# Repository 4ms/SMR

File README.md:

# SMR
## Spectral Multiband Resonator

Firmware for the Spectral Multiband Resonator, a Eurorack-format module from 4ms Company.

The SMR is a 6-channel highly resonant filter ("resonator") with a ring of RGB LEDs, six sliders, and stereo audio inputs and outputs. The main processor is the STM32F427 chip. For more details see http://www.4mspedals.com/smr.php

The SMR would make a nice platform for other audio projects, the hardware contains:

*	180MHz 32-bit ARM chip with FPU (STM32F427)
*	Stereo codec chip (running at 96kHz/24bit in this firmware)
	*	Two audio inputs, two audio outputs
*	Five 16-channel PCA9685 LED drivers (10-bits per channel)  
*	26 RGB LEDs, 20 are arranged in a circle/ellipse, 6 are arranged in a line  
*	Six slider potentiometers with an LED on the shaft  
*	Five potentiometers  
*	Six momentary LED buttons  
*	A rotary encoder and button  
*	Six toggle switches (one is SP3T, others are SPST)  
*	Twelve CV inputs
*	Six gate/digital inputs (can be used as unscaled CV inputs)
*	Six CV outputs (0V-8V), driven by PWM  
  
As of writing this (March 2016), there are three PCB versions: 1.0, 1.0.1, and 1.0.2. These are functionally identical and this firmware will run exactly the same on all versions.

## Setting up your environment
You need to install the GCC ARM toolchain.
This project is known to compile with arm-none-eabi-gcc version 4.8.3, and version 4.9.3. It is likely that it will compile with future versions as well.

It's recommended (but not necessary) to install ST-UTIL/stlink. Without it, you will have to update using the audio bootloader, which is very slow (5 minutes per update).
With ST-UTIL or stlink and a programmer, you can update in 5-20 seconds.
The Texane stlink package contains a gdb debugger, which works with ST-LINK programmers such as the [STM32 Discovery boards](http://www.mouser.com/ProductDetail/STMicroelectronics/STM32F4DISCOVERY/?qs=J2qbEwLrpCGdWLY96ibNeQ%3D%3D&gclid=CKb6u6Cz48cCFZGBfgodfHwH-g&kpid=608656256) to connect to the Spectral's 4-pin SWD header. The STM32F4 Discovery Board is low-cost (under US$15) and works great as a programmer and debugger.

You also may wish to install and IDE such as Eclipse. There are many resources online for setting up GCC ARM with Eclipse (as well as commerical software). This is totally optional. Instead of an IDE you can use your favorite text editor and a few commands on the command line (Terminal) which are given below.

Continue below for Max OSX, Linux, or Windows instructions.

### Mac OSX

For Mac OSX, follow these instructions to install brew and then the arm toolchain and st-link (taken from https://github.com/nitsky/homebrew-stm32):

	ruby -e "$(curl -fsSL https://raw.githubusercontent.com/Homebrew/install/master/install)"
	brew tap nitsky/stm32
	brew install arm-none-eabi-gcc
	brew install stlink

That's it! Continue below to **Clone the Projects**

### Linux

For linux, check your package manager to see if there is a package for arm-none-eabi-gcc or gcc-arm-embedded or gcc-arm-none-eabi. Or just download it here:

[Download GCC ARM toolchain from Launchpad](https://launchpad.net/gcc-arm-embedded/+download)

Next, install st-link from texane:

	sudo apt-get install git libusb-1.0.0-dev pkg-config autotools-dev
	cd (your work directory)
	git clone https://github.com/texane/stlink.git
	cd stlink
	./autogen.sh
	./configure
	make
	export PATH=$PATH:(your work directory)/stlink

The last command makes sure that the binary st-flash is in your PATH so that the Makefile can run it to program your module. 
 
That's it! Continue below to **Clone the Projects**

### Windows
[Download GCC ARM toolchain from Launchpad](https://launchpad.net/gcc-arm-embedded/+download)

[Download ST-UTIL](http://www.st.com/web/en/catalog/tools/PF258168)

Install both. Please contact me if you run into problems that you can't google your way out of! 

## Clone the Projects

Make sure git is installed on your system. (OSX: type "brew install git" into the Terminal)

Create a work directory, and enter it.

Clone this project (SMR), stmlib, and the stm-audio-bootloader projects:

	git clone https://github.com/4ms/SMR.git  
	git clone https://github.com/4ms/stmlib.git
	git clone https://github.com/4ms/stm-audio-bootloader.git
	
Create a symlink for stm-audio-bootloader so that it works with python (required to generate the .wav file for audio bootloading)

     ln -s stm-audio-bootloader stm_audio_bootloader

Verify that your directories are as follows:

	(work directory)
	|  
	|--SMR/  
	|--stm-audio-bootloader/  
	|--stm_audio_bootloader/   <----symlink to stm-audio-bootloader
	|--stmlib/

## Compiling
Make your changes to the code in the SMR directory. When ready to compile, make the project like this:

	cd SMR
	make

If you want to flash the file onto the SMR, attach an [ST-LINK programmer](http://www.st.com/web/catalog/tools/FM116/SC959/SS1532/PF252419) in SWD mode using a 4-conductor cable and run:

	make flash

Read the Discovery Board's manual for how to set it to program external devices. On the STM32F4 Discovery board, you have to remove two DISCOVERY jumpers to put it in ST-LINK mode. Connect the 4-pin cable to the SWD header starting at the dot (pin 1) on the Disco board. On the SMR, pin 1 is labeled with a "1". Any 4-pin cable or even 4 breadboard jumper wires will work. A 10-to-16 pin eurorack power cable is fine too, if it's short enough.

When ready to build an audio file for the bootloader, make it like this:

	make wav

This requires python to run. It creates the file main.wav in the build/ directory. Play the file from a computer or device into the SMR by following the instructions in the User Manual on the [4ms SMR page](http://4mscompany.com/smr.php). 

Troubleshooting: If you have trouble getting python to create a wav file, such as this error:

	ImportError: No module named stm_audio_bootloader

Then try this command:
	
	export PYTHONPATH=$PYTHONPATH:'.'

## Bootloader
The bootloader is a [separate project](https://github.com/4ms/stm-audio-bootloader), slightly modifed from the stm-audio-bootloader from [pichenettes](https://github.com/pichenettes/eurorack). 

The bootloader is already installed on all factory-built SMRs.

## License
The code (software) is licensed by the MIT license.

The hardware is licensed by the [CC BY-NC-SA license](https://creativecommons.org/licenses/by-nc-sa/4.0/) (Creative Commons, Attribution, NonCommercial, ShareAlike).

See LICENSE file.

I would like to see others build and modify the SMR and SMR-influenced works, in a non-commercial manner. My intent is not to limit the educational use nor to prevent people buying hardware components/PCBs collectively in a group. If you have any questions regarding the license or appropriate use, please do not hesitate to contact me! 

## Guidelines for derivative works

Do not include the text "4ms" or "4ms Company" or the graphic 4ms logo on any derivative works. This includes faceplates, enclosures, or front-panels. It's OK (but not required) to include the text "Spectral Multiband Resonator" or "SMR" if you wish.

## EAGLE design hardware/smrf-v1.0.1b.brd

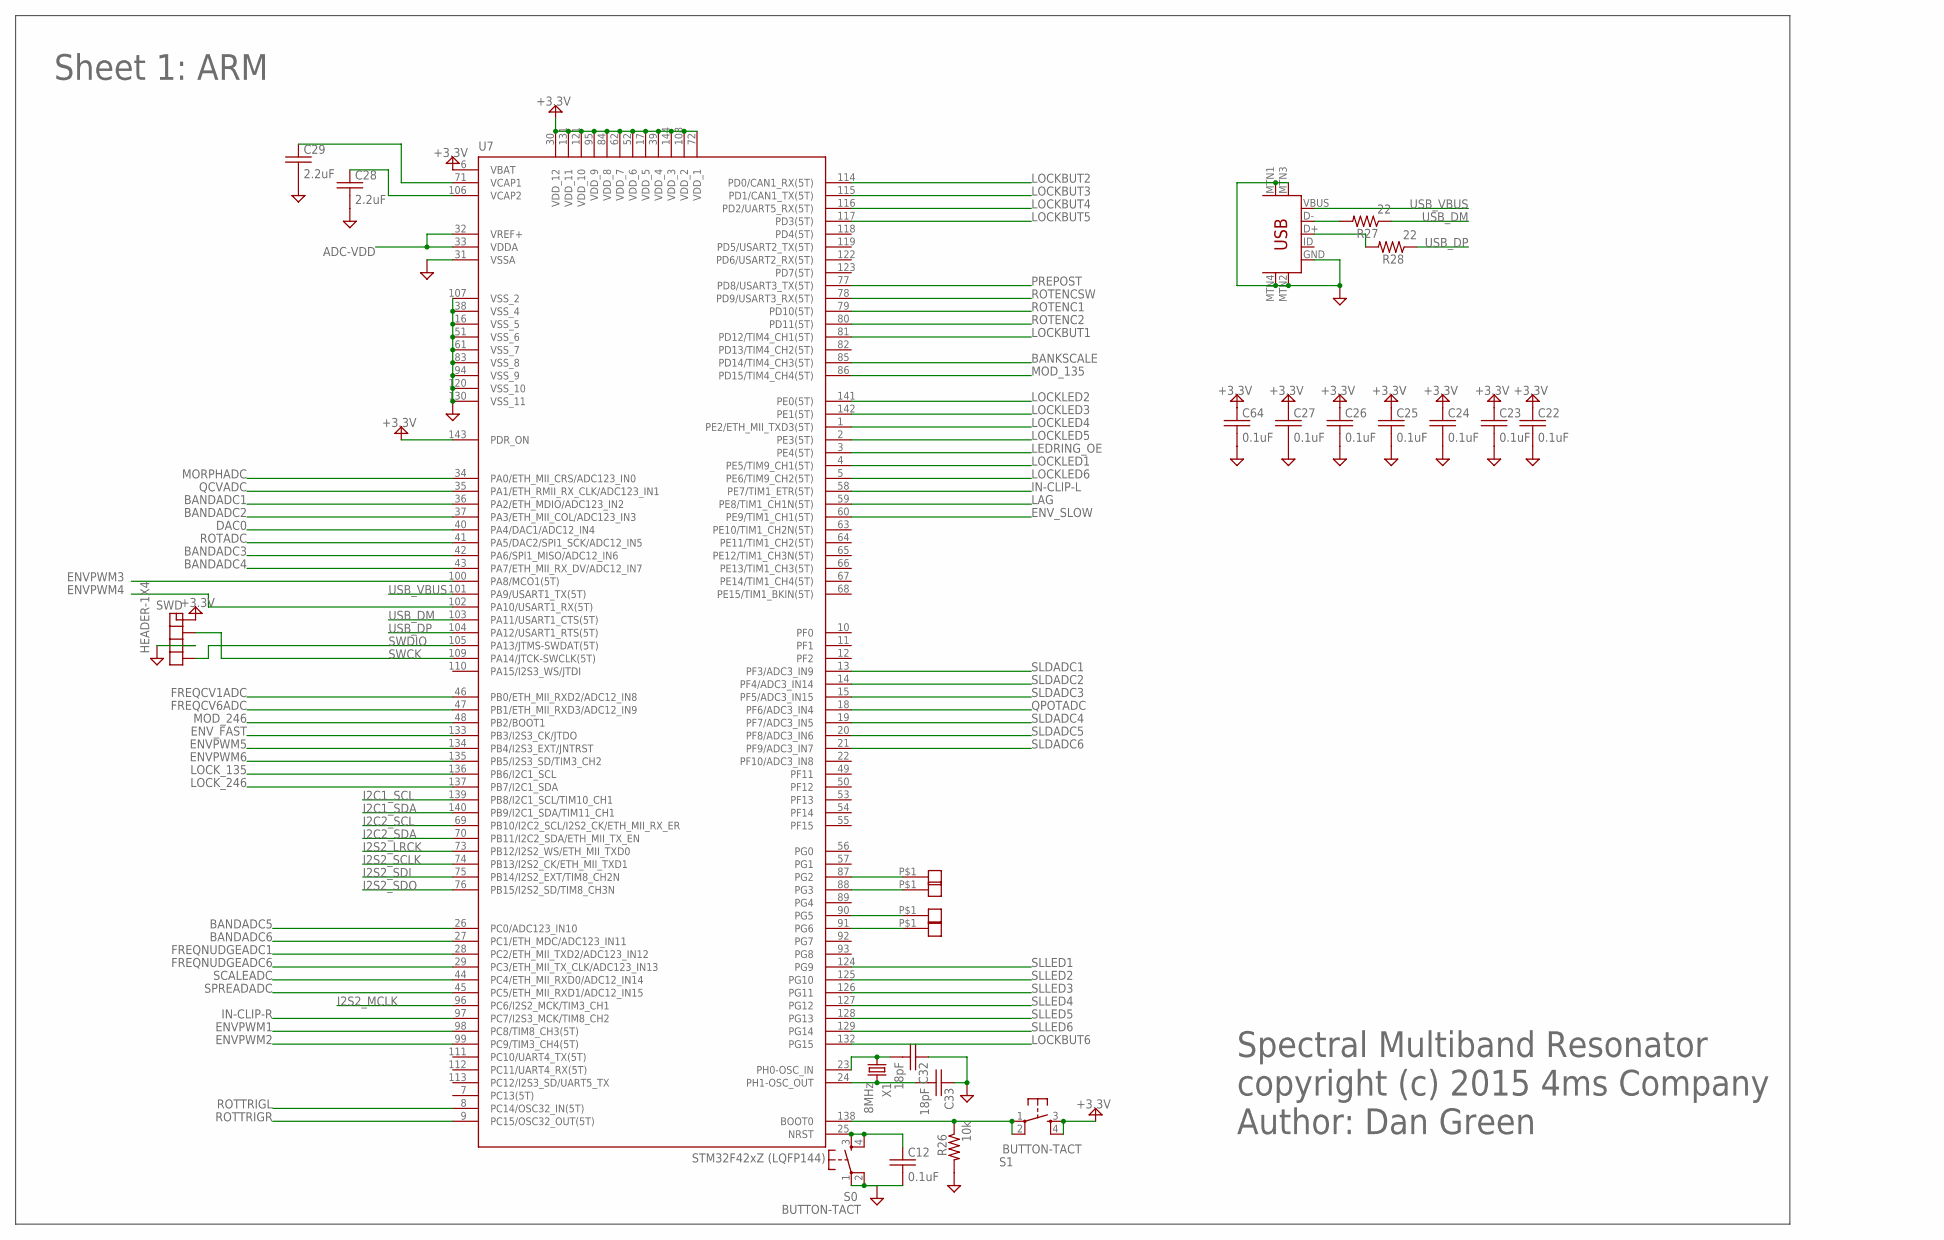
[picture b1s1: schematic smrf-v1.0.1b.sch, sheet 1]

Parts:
C12, C22, C23, C24, C25, C26, C27, C64: 0.1uF; C0603
C28, C29: 2.2uF; C0603
C32, C33: 18pF; C0603
PG2, PG3, PG5, PG6: PAD-06
R26: 10k; R0603
R27, R28: 22; R0603
S0, S1: BUTTON-TACT; BUTTON-TACT-SKQG
SWD: HEADER-1X4; HEADER-1X4-TH
U7: STM32F427ZG; LQFP144
U$1: USB-MINIB-5PIN; USB-MINIB
X1: 8MHz; HC-49/US

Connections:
+3.3V: C22.1, C23.1, C24.1, C25.1, C26.1, C27.1, C64.1, S1.3, S1.4, SWD.P$1, U7.6 (VBAT), U7.17 (VDD_5), U7.30 (VDD_12), U7.39 (VDD_4), U7.52 (VDD_6), U7.62 (VDD_7), U7.72 (VDD_1), U7.84 (VDD_8), U7.95 (VDD_9), U7.108 (VDD_2), U7.121 (VDD_10), U7.131 (VDD_11), U7.143 (PDR_ON), U7.144 (VDD_3); also elsewhere on the board
ADC-VDD: U7.32 (VREF+), U7.33 (VDDA); also elsewhere on the board
BANDADC1: U7.36 (PA2/ETH_MDIO/ADC123_IN2); also elsewhere on the board
BANDADC2: U7.37 (PA3/ETH_MII_COL/ADC123_IN3); also elsewhere on the board
BANDADC3: U7.42 (PA6/SPI1_MISO/ADC12_IN6); also elsewhere on the board
BANDADC4: U7.43 (PA7/ETH_MII_RX_DV/ADC12_IN7); also elsewhere on the board
BANDADC5: U7.26 (PC0/ADC123_IN10); also elsewhere on the board
BANDADC6: U7.27 (PC1/ETH_MDC/ADC123_IN11); also elsewhere on the board
BANKSCALE: U7.85 (PD14/TIM4_CH3(5T)); also elsewhere on the board
DAC0: U7.40 (PA4/DAC1/ADC12_IN4); also elsewhere on the board
ENVPWM1: U7.98 (PC8/TIM8_CH3(5T)); also elsewhere on the board
ENVPWM2: U7.99 (PC9/TIM3_CH4(5T)); also elsewhere on the board
ENVPWM3: U7.100 (PA8/MCO1(5T)); also elsewhere on the board
ENVPWM4: U7.102 (PA10/USART1_RX(5T)); also elsewhere on the board
ENVPWM5: U7.134 (PB4/I2S3_EXT/JNTRST); also elsewhere on the board
ENVPWM6: U7.135 (PB5/I2S3_SD/TIM3_CH2); also elsewhere on the board
ENV_FAST: U7.133 (PB3/I2S3_CK/JTDO); also elsewhere on the board
ENV_SLOW: U7.60 (PE9/TIM1_CH1(5T)); also elsewhere on the board
FREQCV1ADC: U7.46 (PB0/ETH_MII_RXD2/ADC12_IN8); also elsewhere on the board
FREQCV6ADC: U7.47 (PB1/ETH_MII_RXD3/ADC12_IN9); also elsewhere on the board
FREQNUDGEADC1: U7.28 (PC2/ETH_MII_TXD2/ADC123_IN12); also elsewhere on the board
FREQNUDGEADC6: U7.29 (PC3/ETH_MII_TX_CLK/ADC123_IN13); also elsewhere on the board
GND: C12.2, C22.2, C23.2, C24.2, C25.2, C26.2, C27.2, C28.2, C29.2, C32.1, C33.1, C64.2, R26.2, S0.1, S0.2, SWD.P$3, U7.16 (VSS_5), U7.31 (VSSA), U7.38 (VSS_4), U7.51 (VSS_6), U7.61 (VSS_7), U7.83 (VSS_8), U7.94 (VSS_9), U7.107 (VSS_2), U7.120 (VSS_10), U7.130 (VSS_11), U$1.GND, U$1.MTN1 (MTN2), U$1.MTN2 (MTN3), U$1.MTN3 (MTN1), U$1.MTN4; also elsewhere on the board
I2C1_SCL: U7.139 (PB8/I2C1_SCL/TIM10_CH1); also elsewhere on the board
I2C1_SDA: U7.140 (PB9/I2C1_SDA/TIM11_CH1); also elsewhere on the board
I2C2_SCL: U7.69 (PB10/I2C2_SCL/I2S2_CK/ETH_MII_RX_ER); also elsewhere on the board
I2C2_SDA: U7.70 (PB11/I2C2_SDA/ETH_MII_TX_EN); also elsewhere on the board
I2S2_LRCK: U7.73 (PB12/I2S2_WS/ETH_MII_TXD0); also elsewhere on the board
I2S2_MCLK: U7.96 (PC6/I2S2_MCK/TIM3_CH1); also elsewhere on the board
I2S2_SCLK: U7.74 (PB13/I2S2_CK/ETH_MII_TXD1); also elsewhere on the board
I2S2_SDI: U7.75 (PB14/I2S2_EXT/TIM8_CH2N); also elsewhere on the board
I2S2_SDO: U7.76 (PB15/I2S2_SD/TIM8_CH3N); also elsewhere on the board
IN-CLIP-L: U7.58 (PE7/TIM1_ETR(5T)); also elsewhere on the board
IN-CLIP-R: U7.97 (PC7/I2S3_MCK/TIM8_CH2); also elsewhere on the board
LAG: U7.59 (PE8/TIM1_CH1N(5T)); also elsewhere on the board
LEDRING_OE: U7.3 (PE4(5T)); also elsewhere on the board
LOCKBUT1: U7.81 (PD12/TIM4_CH1(5T)); also elsewhere on the board
LOCKBUT2: U7.114 (PD0/CAN1_RX(5T)); also elsewhere on the board
LOCKBUT3: U7.115 (PD1/CAN1_TX(5T)); also elsewhere on the board
LOCKBUT4: U7.116 (PD2/UART5_RX(5T)); also elsewhere on the board
LOCKBUT5: U7.117 (PD3(5T)); also elsewhere on the board
LOCKBUT6: U7.132 (PG15); also elsewhere on the board
LOCKLED1: U7.4 (PE5/TIM9_CH1(5T)); also elsewhere on the board
LOCKLED2: U7.141 (PE0(5T)); also elsewhere on the board
LOCKLED3: U7.142 (PE1(5T)); also elsewhere on the board
LOCKLED4: U7.1 (PE2/ETH_MII_TXD3(5T)); also elsewhere on the board
LOCKLED5: U7.2 (PE3(5T)); also elsewhere on the board
LOCKLED6: U7.5 (PE6/TIM9_CH2(5T)); also elsewhere on the board
LOCK_135: U7.136 (PB6/I2C1_SCL); also elsewhere on the board
LOCK_246: U7.137 (PB7/I2C1_SDA); also elsewhere on the board
MOD_135: U7.86 (PD15/TIM4_CH4(5T)); also elsewhere on the board
MOD_246: U7.48 (PB2/BOOT1); also elsewhere on the board
MORPHADC: U7.34 (PA0/ETH_MII_CRS/ADC123_IN0); also elsewhere on the board
unnamed: R27.2, U$1.D-
unnamed: R28.2, U$1.D+
unnamed: C32.2, U7.23 (PH0-OSC_IN), X1.1
unnamed: C28.1, U7.106 (VCAP2)
unnamed: C29.1, U7.71 (VCAP1)
unnamed: R26.1, S1.1, S1.2, U7.138 (BOOT0)
unnamed: C33.2, U7.24 (PH1-OSC_OUT), X1.2
unnamed: PG2.P$1, U7.87 (PG2)
unnamed: PG3.P$1, U7.88 (PG3)
unnamed: PG6.P$1, U7.91 (PG6)
unnamed: PG5.P$1, U7.90 (PG5)
NRST: C12.1, S0.3, S0.4, U7.25 (NRST)
PREPOST: U7.77 (PD8/USART3_TX(5T)); also elsewhere on the board
QCVADC: U7.35 (PA1/ETH_RMII_RX_CLK/ADC123_IN1); also elsewhere on the board
QPOTADC: U7.18 (PF6/ADC3_IN4); also elsewhere on the board
ROTADC: U7.41 (PA5/DAC2/SPI1_SCK/ADC12_IN5); also elsewhere on the board
ROTENC1: U7.79 (PD10(5T)); also elsewhere on the board
ROTENC2: U7.80 (PD11(5T)); also elsewhere on the board
ROTENCSW: U7.78 (PD9/USART3_RX(5T)); also elsewhere on the board
ROTTRIGL: U7.8 (PC14/OSC32_IN(5T)); also elsewhere on the board
ROTTRIGR: U7.9 (PC15/OSC32_OUT(5T)); also elsewhere on the board
SCALEADC: U7.44 (PC4/ETH_MII_RXD0/ADC12_IN14); also elsewhere on the board
SLDADC1: U7.13 (PF3/ADC3_IN9); also elsewhere on the board
SLDADC2: U7.14 (PF4/ADC3_IN14); also elsewhere on the board
SLDADC3: U7.15 (PF5/ADC3_IN15); also elsewhere on the board
SLDADC4: U7.19 (PF7/ADC3_IN5); also elsewhere on the board
SLDADC5: U7.20 (PF8/ADC3_IN6); also elsewhere on the board
SLDADC6: U7.21 (PF9/ADC3_IN7); also elsewhere on the board
SLLED1: U7.124 (PG9); also elsewhere on the board
SLLED2: U7.125 (PG10); also elsewhere on the board
SLLED3: U7.126 (PG11); also elsewhere on the board
SLLED4: U7.127 (PG12); also elsewhere on the board
SLLED5: U7.128 (PG13); also elsewhere on the board
SLLED6: U7.129 (PG14); also elsewhere on the board
SPREADADC: U7.45 (PC5/ETH_MII_RXD1/ADC12_IN15); also elsewhere on the board
SWCK: SWD.P$2, U7.109 (PA14/JTCK-SWCLK(5T))
SWDIO: SWD.P$4, U7.105 (PA13/JTMS-SWDAT(5T))
USB_DM: R27.1, U7.103 (PA11/USART1_CTS(5T))
USB_DP: R28.1, U7.104 (PA12/USART1_RTS(5T))
USB_VBUS: U7.101 (PA9/USART1_TX(5T)), U$1.VBUS

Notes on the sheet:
Spectral Multiband Resonator
copyright (c) 2015 4ms Company Author: Dan Green
Sheet 1: ARM

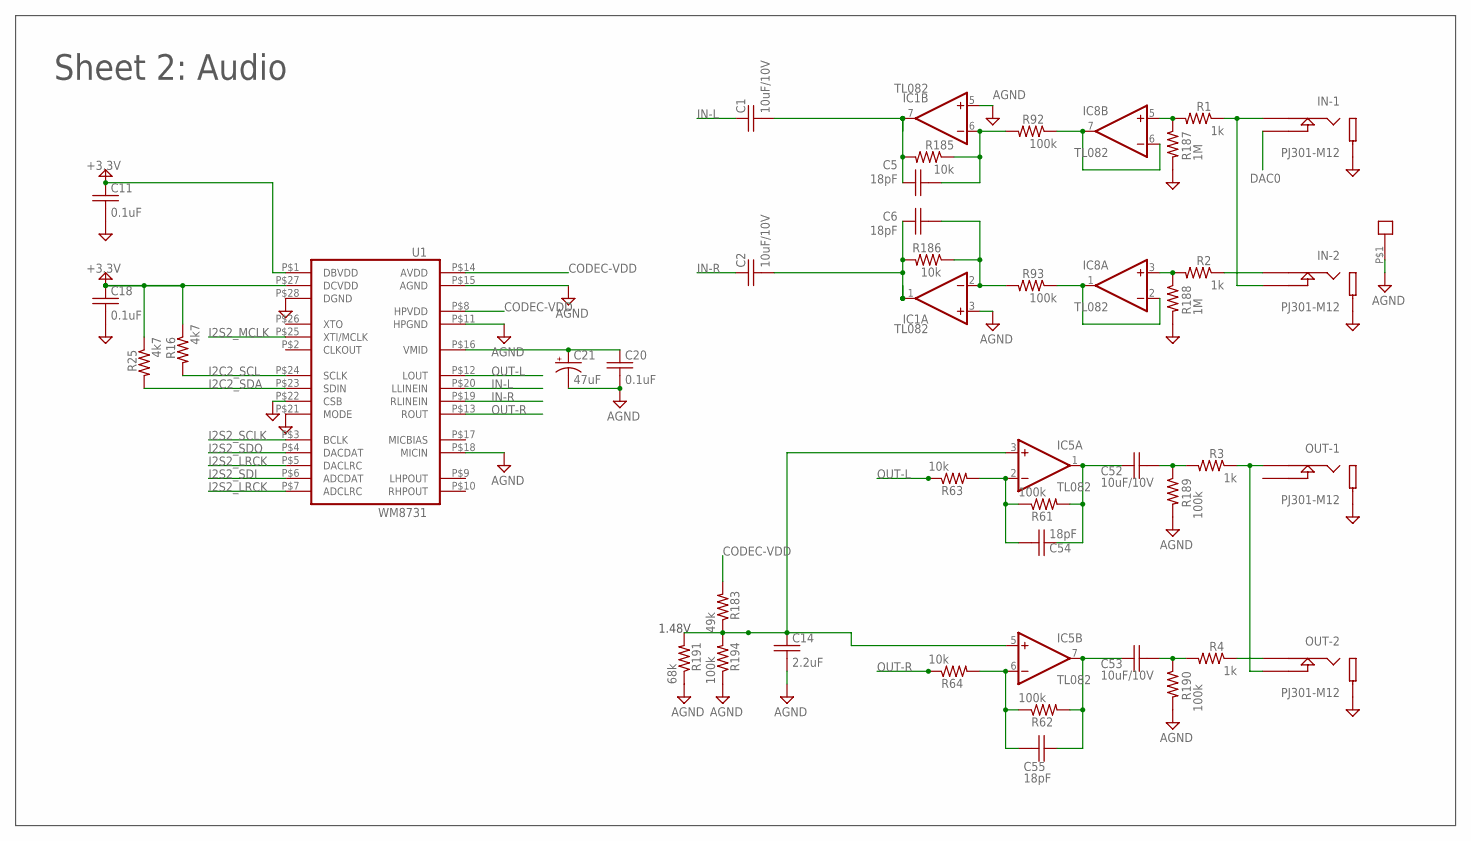
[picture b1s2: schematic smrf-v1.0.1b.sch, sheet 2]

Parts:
AGND-OPT: PAD-06
C1, C2, C52, C53: 10uF/10V; C0603
C5, C6, C54, C55: 18pF; C0603
C11, C18, C20: 0.1uF; C0603
C14: 2.2uF; C0603
C21: 47uF; C-POL-5
IC1, IC5, IC8: TL082; TSSOP8
IN-1, IN-2: PJ301-M12; PJ301M-12-FIX
OUT-1, OUT-2: PJ301-M12; PJ301M-12-FIX
R1, R2, R3, R4: 1k; R0603
R16, R25: 4k7; R0603
R61, R62, R92, R93, R189, R190, R194: 100k; R0603
R63, R64, R185, R186: 10k; R0603
R183: 49k; R0603
R187, R188: 1M; R0603
R191: 68k; R0603
U1: WM8731; 28-SSOP

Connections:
+3.3V: C11.1, C18.1, R16.1, R25.1, U1.P$1 (DBVDD), U1.P$27 (DCVDD); also elsewhere on the board
AGND: AGND-OPT.P$1, C14.2, C20.2, C21.-, IC1.3 (+IN), IC1.5 (+IN), R189.2, R190.2, R191.1, R194.1, U1.P$11 (HPGND), U1.P$15 (AGND), U1.P$18 (MICIN); also elsewhere on the board
CODEC-VDD: R183.2, U1.P$8 (HPVDD), U1.P$14 (AVDD); also elsewhere on the board
DAC0: IN-1.3 (TIP-SW); also elsewhere on the board
GND: C11.2, C18.2, IN-1.2 (SLEEVE), IN-2.2 (SLEEVE), OUT-1.2 (SLEEVE), OUT-2.2 (SLEEVE), R187.2, R188.2, U1.P$21 (MODE), U1.P$22 (CSB), U1.P$28 (DGND); also elsewhere on the board
I2C2_SCL: R16.2, U1.P$24 (SCLK); also elsewhere on the board
I2C2_SDA: R25.2, U1.P$23 (SDIN); also elsewhere on the board
I2S2_LRCK: U1.P$5 (DACLRC), U1.P$7 (ADCLRC); also elsewhere on the board
I2S2_MCLK: U1.P$25 (XTI/MCLK); also elsewhere on the board
I2S2_SCLK: U1.P$3 (BCLK); also elsewhere on the board
I2S2_SDI: U1.P$6 (ADCDAT); also elsewhere on the board
I2S2_SDO: U1.P$4 (DACDAT); also elsewhere on the board
IN-L: C1.1, U1.P$20 (LLINEIN)
IN-R: C2.1, U1.P$19 (RLINEIN)
unnamed: OUT-2.1 (TIP), R4.1
unnamed: OUT-1.1 (TIP), OUT-2.3 (TIP-SW), R3.1
unnamed: IN-2.1 (TIP), R2.1
unnamed: C6.2, IC1.2 (-IN), R93.2, R186.1
unnamed: C20.1, C21.+, U1.P$16 (VMID)
unnamed: C54.2, IC5.2 (-IN), R61.1, R63.2
unnamed: C5.2, IC1.6 (-IN), R92.2, R185.1
unnamed: IN-1.1 (TIP), IN-2.3 (TIP-SW), R1.1
unnamed: C1.2, C5.1, IC1.7 (OUT), R185.2
unnamed: C2.2, C6.1, IC1.1 (OUT), R186.2
unnamed: C52.1, C54.1, IC5.1 (OUT), R61.2
unnamed: C55.2, IC5.6 (-IN), R62.1, R64.2
unnamed: C53.1, C55.1, IC5.7 (OUT), R62.2
unnamed: IC8.5 (+IN), R1.2, R187.1
unnamed: IC8.3 (+IN), R2.2, R188.1
unnamed: IC8.6 (-IN), IC8.7 (OUT), R92.1
unnamed: IC8.1 (OUT), IC8.2 (-IN), R93.1
unnamed: C52.2, R3.2, R189.1
unnamed: C53.2, R4.2, R190.1
OUT-L: R63.1, U1.P$12 (LOUT)
OUT-R: R64.1, U1.P$13 (ROUT)
VOUTOFFSET: C14.1, IC5.3 (+IN), IC5.5 (+IN), R183.1, R191.2, R194.2

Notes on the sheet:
1.48V
Sheet 2: Audio

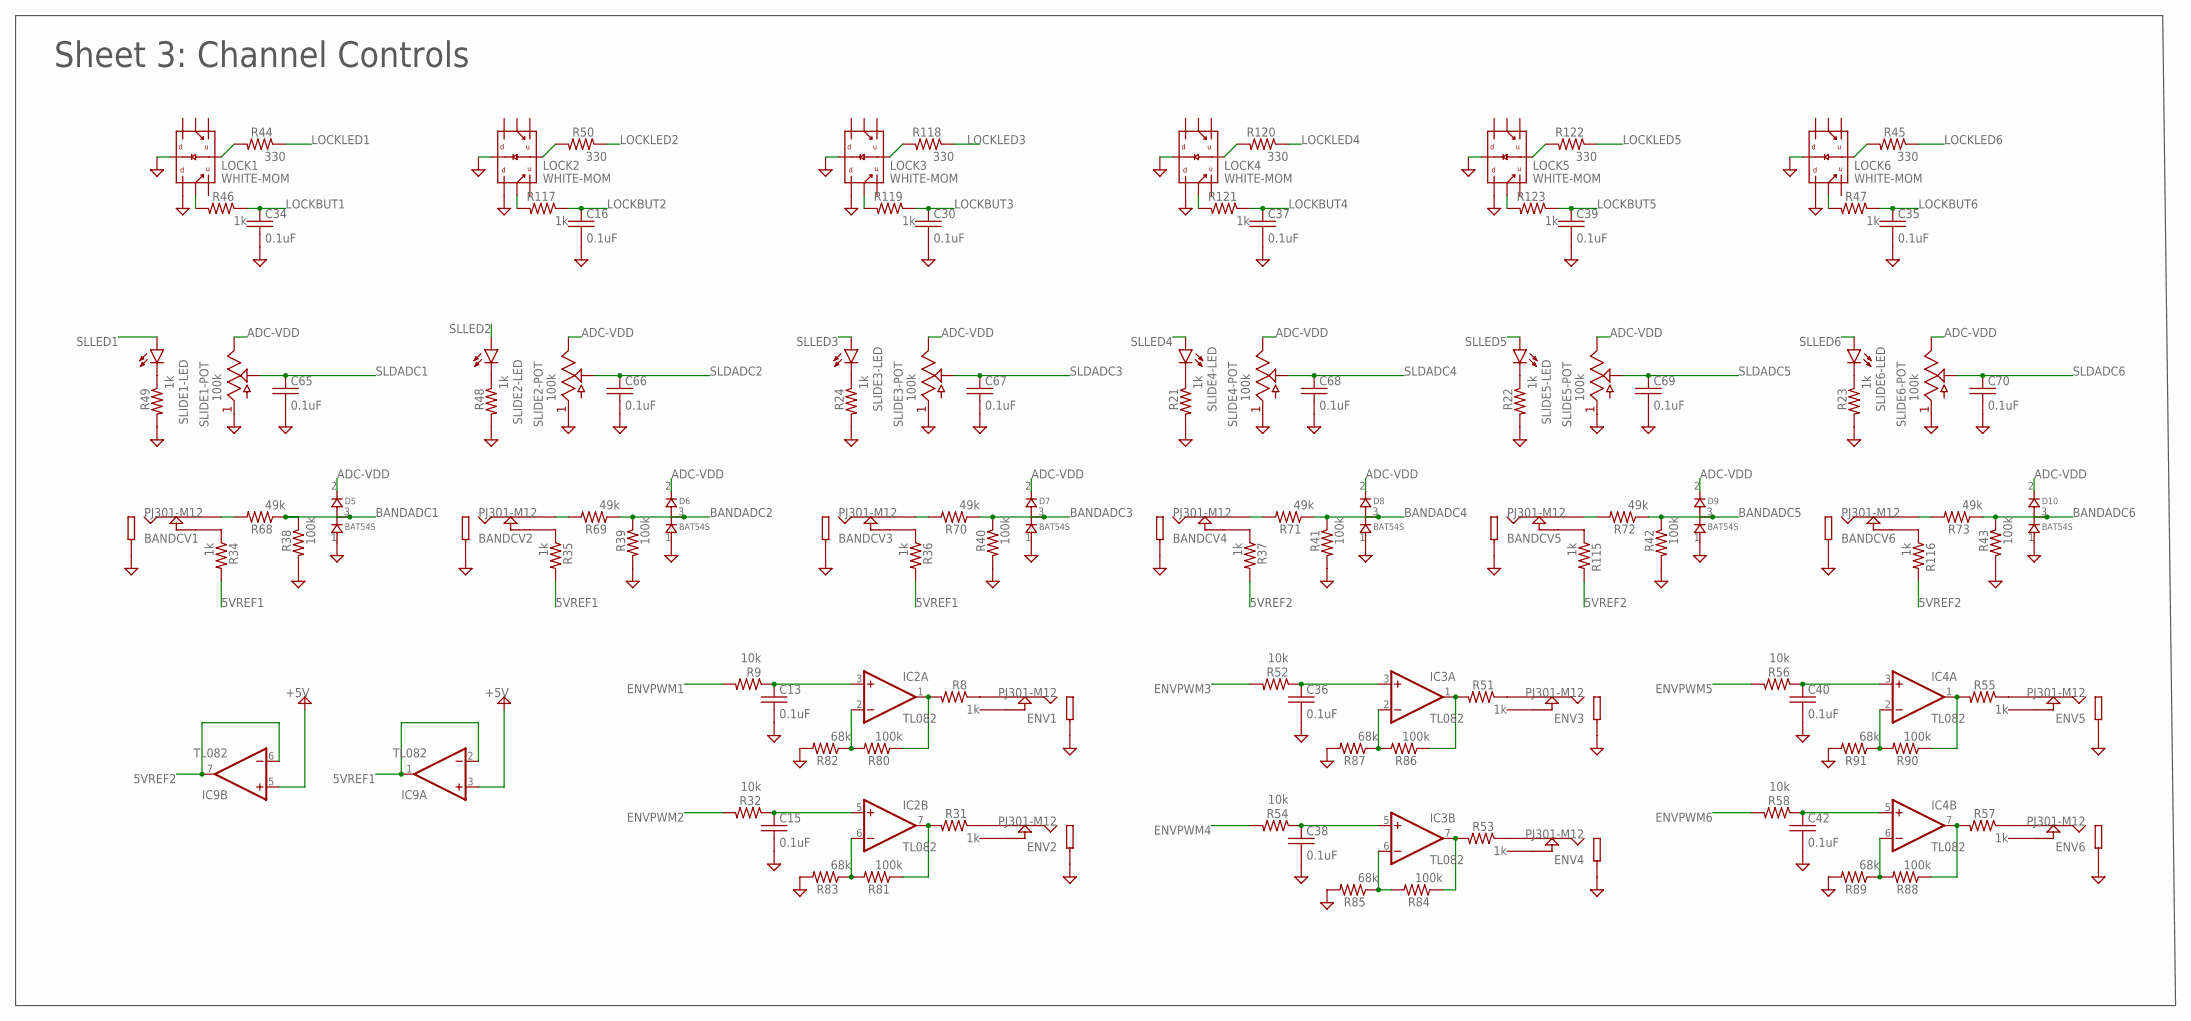
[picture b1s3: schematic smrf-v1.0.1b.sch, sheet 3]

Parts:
BANDCV1, BANDCV2, BANDCV3, BANDCV4, BANDCV5, BANDCV6: PJ301-M12; PJ301M-12-FIX
C13, C15, C16, C30, C34, C35, C36, C37, C38, C39, C40, C42, C65, C66, C67, C68, C69, C70: 0.1uF; C0603
D5, D6, D7, D8, D9, D10: BAT54S; SOT23
ENV1, ENV2, ENV3, ENV4, ENV5, ENV6: PJ301-M12; PJ301M-12-FIX
IC2, IC3, IC4, IC9: TL082; TSSOP8
LOCK1, LOCK2, LOCK3, LOCK4, LOCK5, LOCK6: WHITE-MOM; BUTTON-LED-PB61303
R8, R21, R22, R23, R24, R31, R34, R35, R36, R37, R46, R47, R48, R49, R51, R53, R55, R57, R115, R116, R117, R119, R121, R123: 1k; R0603
R9, R32, R52, R54, R56, R58: 10k; R0603
R38, R39, R40, R41, R42, R43, R80, R81, R84, R86, R88, R90: 100k; R0603
R44, R45, R50, R118, R120, R122: 330; R0603
R68, R69, R70, R71, R72, R73: 49k; R0603
R82, R83, R85, R87, R89, R91: 68k; R0603
SLIDE1, SLIDE2, SLIDE3, SLIDE4, SLIDE5, SLIDE6: 100k; POT-SLIDER-ALPHA-RA2045F-20

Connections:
5VREF1: IC9.1 (OUT), IC9.2 (-IN), R34.2, R35.2, R36.2
5VREF2: IC9.6 (-IN), IC9.7 (OUT), R37.2, R115.2, R116.2
+5V: IC9.3 (+IN), IC9.5 (+IN); also elsewhere on the board
ADC-VDD: D5.2 (CATHODE), D6.2 (CATHODE), D7.2 (CATHODE), D8.2 (CATHODE), D9.2 (CATHODE), D10.2 (CATHODE), SLIDE1.P$3 (3), SLIDE2.P$3 (3), SLIDE3.P$3 (3), SLIDE4.P$3 (3), SLIDE5.P$3 (3), SLIDE6.P$3 (3); also elsewhere on the board
BANDADC1: D5.3 (COMMON), R38.1, R68.1; also elsewhere on the board
BANDADC2: D6.3 (COMMON), R39.1, R69.1; also elsewhere on the board
BANDADC3: D7.3 (COMMON), R40.1, R70.1; also elsewhere on the board
BANDADC4: D8.3 (COMMON), R41.1, R71.1; also elsewhere on the board
BANDADC5: D9.3 (COMMON), R42.1, R72.1; also elsewhere on the board
BANDADC6: D10.3 (COMMON), R43.1, R73.1; also elsewhere on the board
ENVPWM1: R9.2; also elsewhere on the board
ENVPWM2: R32.2; also elsewhere on the board
ENVPWM3: R52.2; also elsewhere on the board
ENVPWM4: R54.2; also elsewhere on the board
ENVPWM5: R56.2; also elsewhere on the board
ENVPWM6: R58.2; also elsewhere on the board
GND: BANDCV1.2 (SLEEVE), BANDCV2.2 (SLEEVE), BANDCV3.2 (SLEEVE), BANDCV4.2 (SLEEVE), BANDCV5.2 (SLEEVE), BANDCV6.2 (SLEEVE), C13.2, C15.2, C16.2, C30.2, C34.2, C35.2, C36.2, C37.2, C38.2, C39.2, C40.2, C42.2, C65.2, C66.2, C67.2, C68.2, C69.2, C70.2, D5.1 (ANODE), D6.1 (ANODE), D7.1 (ANODE), D8.1 (ANODE), D9.1 (ANODE), D10.1 (ANODE), ENV1.2 (SLEEVE), ENV2.2 (SLEEVE), ENV3.2 (SLEEVE), ENV4.2 (SLEEVE), ENV5.2 (SLEEVE), ENV6.2 (SLEEVE), LOCK1.P$6, LOCK1.P$8, LOCK2.P$6, LOCK2.P$8, LOCK3.P$6, LOCK3.P$8, LOCK4.P$6, LOCK4.P$8, LOCK5.P$6, LOCK5.P$8, LOCK6.P$6, LOCK6.P$8, R21.2, R22.2, R23.2, R24.2, R38.2, R39.2, R40.2, R41.2, R42.2, R43.2, R48.2, R49.2, R82.2, R83.2, R85.2, R87.2, R89.2, R91.2, SLIDE1.P$1 (1), SLIDE2.P$1 (1), SLIDE3.P$1 (1), SLIDE4.P$1 (1), SLIDE5.P$1 (1), SLIDE6.P$1 (1); also elsewhere on the board
LOCKBUT1: C34.1, R46.1; also elsewhere on the board
LOCKBUT2: C16.1, R117.1; also elsewhere on the board
LOCKBUT3: C30.1, R119.1; also elsewhere on the board
LOCKBUT4: C37.1, R121.1; also elsewhere on the board
LOCKBUT5: C39.1, R123.1; also elsewhere on the board
LOCKBUT6: C35.1, R47.1; also elsewhere on the board
LOCKLED1: R44.1; also elsewhere on the board
LOCKLED2: R50.1; also elsewhere on the board
LOCKLED3: R118.1; also elsewhere on the board
LOCKLED4: R120.1; also elsewhere on the board
LOCKLED5: R122.1; also elsewhere on the board
LOCKLED6: R45.1; also elsewhere on the board
unnamed: ENV1.1 (TIP), R8.1
unnamed: BANDCV1.3 (TIP-SW), R34.1
unnamed: BANDCV2.3 (TIP-SW), R35.1
unnamed: BANDCV3.3 (TIP-SW), R36.1
unnamed: BANDCV4.3 (TIP-SW), R37.1
unnamed: BANDCV5.3 (TIP-SW), R115.1
unnamed: BANDCV6.3 (TIP-SW), R116.1
unnamed: R21.1, SLIDE4.P$LEDC (C)
unnamed: R22.1, SLIDE5.P$LEDC (C)
unnamed: LOCK2.P$7, R50.2
unnamed: LOCK2.P$5, R117.2
unnamed: C13.1, IC2.3 (+IN), R9.1
unnamed: R23.1, SLIDE6.P$LEDC (C)
unnamed: BANDCV1.1 (TIP), R68.2
unnamed: LOCK1.P$7, R44.2
unnamed: BANDCV2.1 (TIP), R69.2
unnamed: LOCK6.P$7, R45.2
unnamed: R24.1, SLIDE3.P$LEDC (C)
unnamed: BANDCV3.1 (TIP), R70.2
unnamed: LOCK1.P$5, R46.2
unnamed: R48.1, SLIDE2.P$LEDC (C)
unnamed: BANDCV4.1 (TIP), R71.2
unnamed: LOCK6.P$5, R47.2
unnamed: R49.1, SLIDE1.P$LEDC (C)
unnamed: BANDCV5.1 (TIP), R72.2
unnamed: BANDCV6.1 (TIP), R73.2
unnamed: IC2.1 (OUT), R8.2, R80.1
unnamed: ENV2.1 (TIP), R31.1
unnamed: C15.1, IC2.5 (+IN), R32.1
unnamed: IC2.7 (OUT), R31.2, R81.1
unnamed: ENV3.1 (TIP), R51.1
unnamed: C36.1, IC3.3 (+IN), R52.1
unnamed: IC3.1 (OUT), R51.2, R86.1
unnamed: ENV4.1 (TIP), R53.1
unnamed: C38.1, IC3.5 (+IN), R54.1
unnamed: IC3.7 (OUT), R53.2, R84.1
unnamed: ENV5.1 (TIP), R55.1
unnamed: C40.1, IC4.3 (+IN), R56.1
unnamed: IC4.1 (OUT), R55.2, R90.1
unnamed: ENV6.1 (TIP), R57.1
unnamed: C42.1, IC4.5 (+IN), R58.1
unnamed: IC4.7 (OUT), R57.2, R88.1
unnamed: IC4.2 (-IN), R90.2, R91.1
unnamed: IC3.6 (-IN), R84.2, R85.1
unnamed: IC3.2 (-IN), R86.2, R87.1
unnamed: IC4.6 (-IN), R88.2, R89.1
unnamed: IC2.6 (-IN), R81.2, R83.1
unnamed: IC2.2 (-IN), R80.2, R82.1
unnamed: LOCK3.P$7, R118.2
unnamed: LOCK3.P$5, R119.2
unnamed: LOCK4.P$7, R120.2
unnamed: LOCK4.P$5, R121.2
unnamed: LOCK5.P$7, R122.2
unnamed: LOCK5.P$5, R123.2
SLDADC1: C65.1, SLIDE1.P$2 (2); also elsewhere on the board
SLDADC2: C66.1, SLIDE2.P$2 (2); also elsewhere on the board
SLDADC3: C67.1, SLIDE3.P$2 (2); also elsewhere on the board
SLDADC4: C68.1, SLIDE4.P$2 (2); also elsewhere on the board
SLDADC5: C69.1, SLIDE5.P$2 (2); also elsewhere on the board
SLDADC6: C70.1, SLIDE6.P$2 (2); also elsewhere on the board
SLLED1: SLIDE1.P$LEDA (A); also elsewhere on the board
SLLED2: SLIDE2.P$LEDA (A); also elsewhere on the board
SLLED3: SLIDE3.P$LEDA (A); also elsewhere on the board
SLLED4: SLIDE4.P$LEDA (A); also elsewhere on the board
SLLED5: SLIDE5.P$LEDA (A); also elsewhere on the board
SLLED6: SLIDE6.P$LEDA (A); also elsewhere on the board

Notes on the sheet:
Sheet 3: Channel Controls

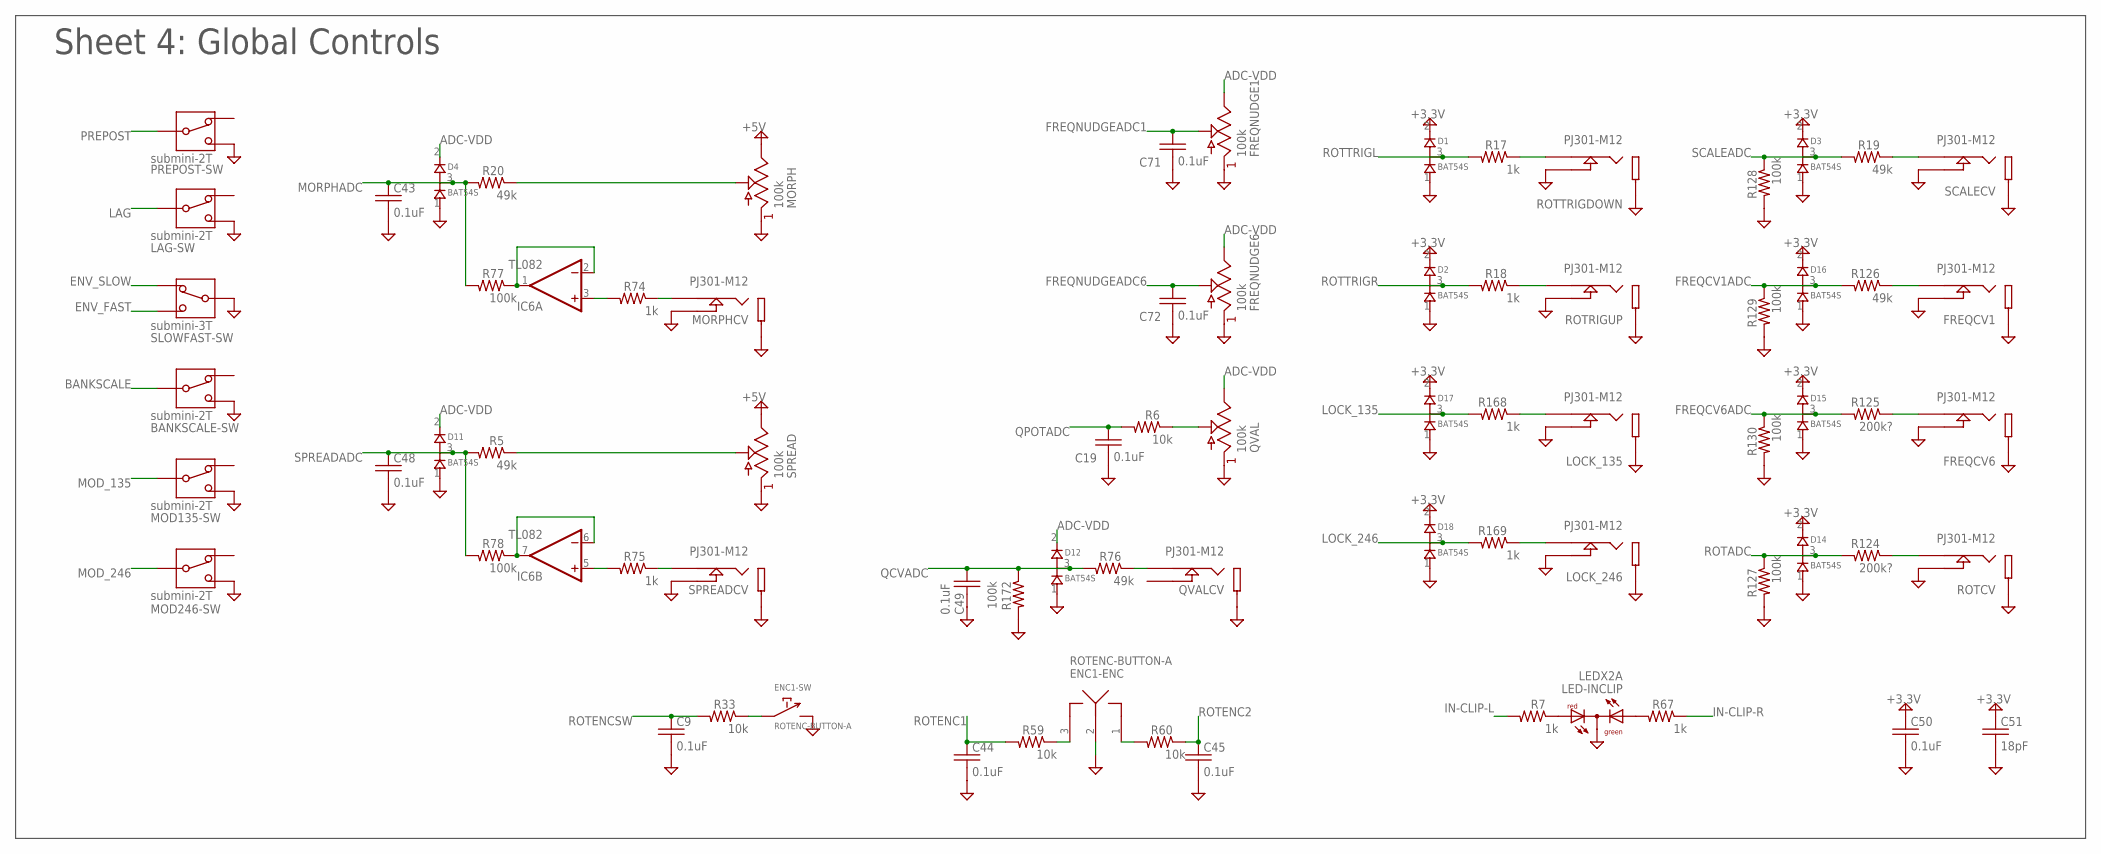
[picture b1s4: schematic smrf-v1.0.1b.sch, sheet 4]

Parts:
BANKSCALE-SW: submini-2T; SPDT-SUB
C9, C19, C43, C44, C45, C48, C49, C50, C71, C72: 0.1uF; C0603
C51: 18pF; C0603
D1, D2, D3, D4, D11, D12, D14, D15, D16, D17, D18: BAT54S; SOT23
ENC1: ROTENC-BUTTON-A; ROTENC-12MM-BUT
FREQCV1, FREQCV6: PJ301-M12; PJ301M-12-FIX
FREQNUDGE1, FREQNUDGE6: 100k; POT-9MM-SONGHUEI
IC6: TL082; TSSOP8
LAG-SW: submini-2T; SPDT-SUB
LED-INCLIP: LEDX2A; LED-T1X2
LOCK_135, LOCK_246: PJ301-M12; PJ301M-12-FIX
MOD135-SW, MOD246-SW: submini-2T; SPDT-SUB
MORPH: 100k; POT-9MM-SONGHUEI
MORPHCV: PJ301-M12; PJ301M-12-FIX
PREPOST-SW: submini-2T; SPDT-SUB
QVAL: 100k; POT-9MM-SONGHUEI
QVALCV: PJ301-M12; PJ301M-12-FIX
R5, R19, R20, R76, R126: 49k; R0603
R6, R33, R59, R60: 10k; R0603
R7, R17, R18, R67, R74, R75, R168, R169: 1k; R0603
R77, R78, R127, R128, R129, R130, R172: 100k; R0603
R124, R125: 200k?; R0603
ROTCV: PJ301-M12; PJ301M-12-FIX
ROTRIGUP: PJ301-M12; PJ301M-12-FIX
ROTTRIGDOWN: PJ301-M12; PJ301M-12-FIX
SCALECV: PJ301-M12; PJ301M-12-FIX
SLOWFAST-SW: submini-3T; SPDT-SUB
SPREAD: 100k; POT-9MM-SONGHUEI
SPREADCV: PJ301-M12; PJ301M-12-FIX

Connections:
+3.3V: C50.1, C51.1, D1.2 (CATHODE), D2.2 (CATHODE), D3.2 (CATHODE), D14.2 (CATHODE), D15.2 (CATHODE), D16.2 (CATHODE), D17.2 (CATHODE), D18.2 (CATHODE); also elsewhere on the board
+5V: MORPH.3, SPREAD.3; also elsewhere on the board
ADC-VDD: D4.2 (CATHODE), D11.2 (CATHODE), D12.2 (CATHODE), FREQNUDGE1.3, FREQNUDGE6.3, QVAL.3; also elsewhere on the board
BANKSCALE: BANKSCALE-SW.P$2; also elsewhere on the board
ENV_FAST: SLOWFAST-SW.P$1; also elsewhere on the board
ENV_SLOW: SLOWFAST-SW.P$3; also elsewhere on the board
FREQCV1ADC: D16.3 (COMMON), R126.2, R129.1; also elsewhere on the board
FREQCV6ADC: D15.3 (COMMON), R125.2, R130.1; also elsewhere on the board
FREQNUDGEADC1: C71.1, FREQNUDGE1.2; also elsewhere on the board
FREQNUDGEADC6: C72.1, FREQNUDGE6.2; also elsewhere on the board
GND: BANKSCALE-SW.P$1, C9.2, C19.2, C43.2, C44.2, C45.2, C48.2, C49.2, C50.2, C51.2, C71.2, C72.2, D1.1 (ANODE), D2.1 (ANODE), D3.1 (ANODE), D4.1 (ANODE), D11.1 (ANODE), D12.1 (ANODE), D14.1 (ANODE), D15.1 (ANODE), D16.1 (ANODE), D17.1 (ANODE), D18.1 (ANODE), ENC1.2, ENC1.SW2, FREQCV1.2 (SLEEVE), FREQCV1.3 (TIP-SW), FREQCV6.2 (SLEEVE), FREQCV6.3 (TIP-SW), FREQNUDGE1.1, FREQNUDGE6.1, LAG-SW.P$1, LED-INCLIP.K-2 (C), LOCK_135.2 (SLEEVE), LOCK_135.3 (TIP-SW), LOCK_246.2 (SLEEVE), LOCK_246.3 (TIP-SW), MOD135-SW.P$1, MOD246-SW.P$1, MORPH.1, MORPHCV.2 (SLEEVE), MORPHCV.3 (TIP-SW), PREPOST-SW.P$1, QVAL.1, QVALCV.2 (SLEEVE), R127.2, R128.2, R129.2, R130.2, R172.2, ROTCV.2 (SLEEVE), ROTCV.3 (TIP-SW), ROTRIGUP.2 (SLEEVE), ROTRIGUP.3 (TIP-SW), ROTTRIGDOWN.2 (SLEEVE), ROTTRIGDOWN.3 (TIP-SW), SCALECV.2 (SLEEVE), SCALECV.3 (TIP-SW), SLOWFAST-SW.P$2, SPREAD.1, SPREADCV.2 (SLEEVE), SPREADCV.3 (TIP-SW); also elsewhere on the board
IN-CLIP-L: R7.2; also elsewhere on the board
IN-CLIP-R: R67.1; also elsewhere on the board
LAG: LAG-SW.P$2; also elsewhere on the board
LOCK_135: D17.3 (COMMON), R168.2; also elsewhere on the board
LOCK_246: D18.3 (COMMON), R169.2; also elsewhere on the board
MOD_135: MOD135-SW.P$2; also elsewhere on the board
MOD_246: MOD246-SW.P$2; also elsewhere on the board
MORPHADC: C43.1, D4.3 (COMMON), R20.2, R77.2; also elsewhere on the board
unnamed: IC6.3 (+IN), R74.2
unnamed: MORPH.2, R20.1
unnamed: IC6.5 (+IN), R75.2
unnamed: QVAL.2, R6.1
unnamed: R17.1, ROTTRIGDOWN.1 (TIP)
unnamed: R18.1, ROTRIGUP.1 (TIP)
unnamed: R19.1, SCALECV.1 (TIP)
unnamed: R5.1, SPREAD.2
unnamed: ENC1.3, R59.1
unnamed: LOCK_135.1 (TIP), R168.1
unnamed: ENC1.SW1, R33.1
unnamed: LOCK_246.1 (TIP), R169.1
unnamed: LED-INCLIP.A-1 (AR), R7.1
unnamed: LED-INCLIP.A-3 (AG), R67.2
unnamed: ENC1.1, R60.2
unnamed: MORPHCV.1 (TIP), R74.1
unnamed: R75.1, SPREADCV.1 (TIP)
unnamed: QVALCV.1 (TIP), R76.1
unnamed: IC6.1 (OUT), IC6.2 (-IN), R77.1
unnamed: IC6.6 (-IN), IC6.7 (OUT), R78.1
unnamed: R124.1, ROTCV.1 (TIP)
unnamed: FREQCV6.1 (TIP), R125.1
unnamed: FREQCV1.1 (TIP), R126.1
PREPOST: PREPOST-SW.P$2; also elsewhere on the board
QCVADC: C49.1, D12.3 (COMMON), R76.2, R172.1; also elsewhere on the board
QPOTADC: C19.1, R6.2; also elsewhere on the board
ROTADC: D14.3 (COMMON), R124.2, R127.1; also elsewhere on the board
ROTENC1: C44.1, R59.2; also elsewhere on the board
ROTENC2: C45.1, R60.1; also elsewhere on the board
ROTENCSW: C9.1, R33.2; also elsewhere on the board
ROTTRIGL: D1.3 (COMMON), R17.2; also elsewhere on the board
ROTTRIGR: D2.3 (COMMON), R18.2; also elsewhere on the board
SCALEADC: D3.3 (COMMON), R19.2, R128.1; also elsewhere on the board
SPREADADC: C48.1, D11.3 (COMMON), R5.2, R78.2; also elsewhere on the board

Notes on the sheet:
Sheet 4: Global Controls

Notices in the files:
adc.c:
See http://creativecommons.org/licenses/MIT/ for more information.
parts and their libraries:
SparkFun-Connectors: Licensing: Creative Commons ShareAlike 4.0 International - https://creativecommons.org/licenses/by-sa/4.0
